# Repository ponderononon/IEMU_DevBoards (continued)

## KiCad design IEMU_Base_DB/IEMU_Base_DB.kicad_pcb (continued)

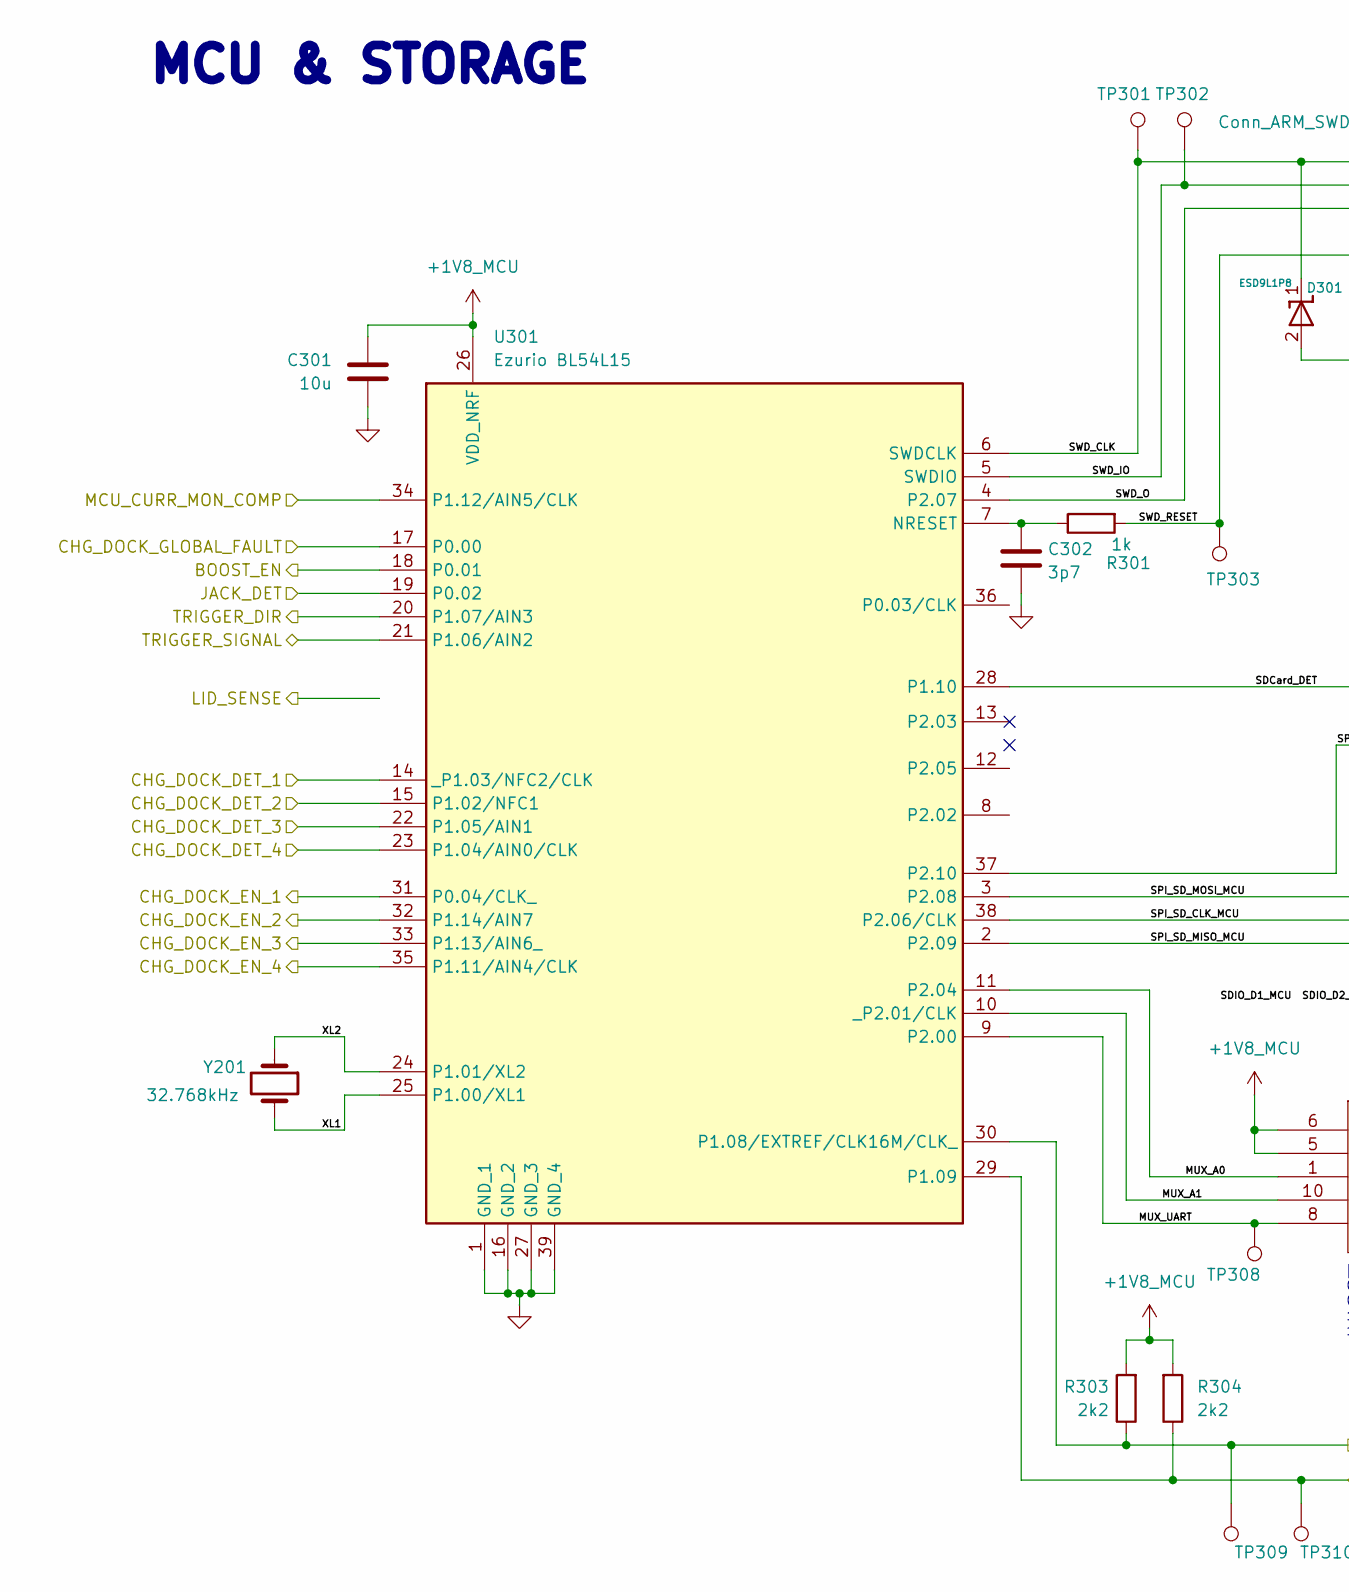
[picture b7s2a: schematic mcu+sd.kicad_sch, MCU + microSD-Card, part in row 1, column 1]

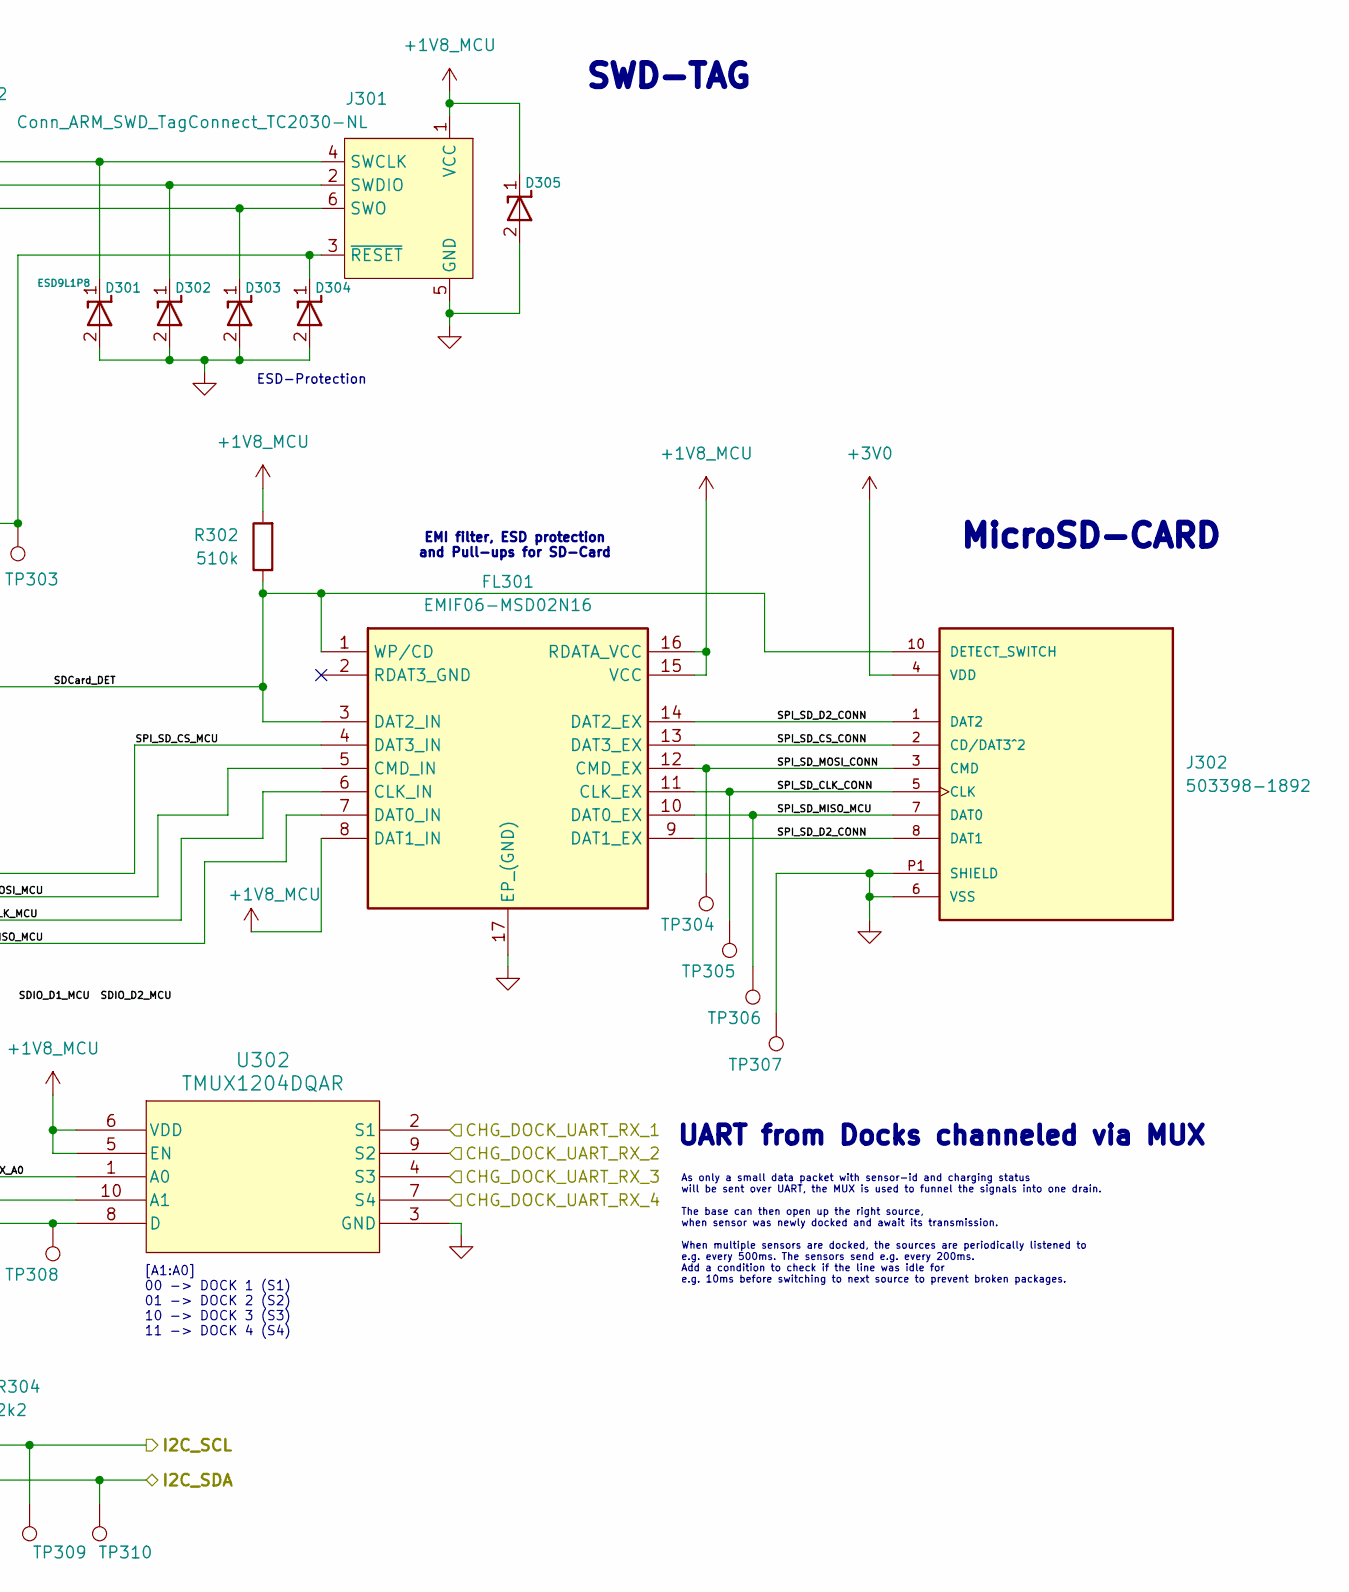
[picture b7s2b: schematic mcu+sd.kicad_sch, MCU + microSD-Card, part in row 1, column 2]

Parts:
C301: 10u; C_0603_1608Metric; Manufacturer_Part_Number CL10A106MA8NRNC; LCSC C96446
C302: 3p7; C_0402_1005Metric; Manufacturer_Part_Number GCM1555C1H3R7CA16D; LCSC C2189484
D301, D302, D303, D304, D305: ESD9L1P8; D_SOD-882; Manufacturer_Part_Number ESD9L1P8; LCSC C6244607
FL301: EMIF06-MSD02N16; EMIF06MSD02N16; Manufacturer_Part_Number EMIF06-MSD02N16; LCSC C5267594
J301: Conn_ARM_SWD_TagConnect_TC2030-NL; Tag-Connect_TC2030-IDC-NL_2x03_P1.27mm_Vertical
J302: 503398-1892; MOLEX_503398-1892; Manufacturer_Part_Number 503398-1892; LCSC C428492
R301: 1k; R_0402_1005Metric; Manufacturer_Part_Number 0402WGF1001TCE; LCSC C11702
R302: 510k; R_0603_1608Metric; Manufacturer_Part_Number 0603WAF5103T5E; LCSC C23192
R303, R304: 2k2; R_0402_1005Metric; Manufacturer_Part_Number 0402WGF2201TCE; LCSC C25879
TP301, TP302, TP303, TP309, TP310: TestPoint_Pad_D1.0mm
TP304, TP305, TP306, TP307, TP308: TestPoint; TestPoint_Pad_D1.0mm
U301: Ezurio BL54L15; BL54L15; Manufacturer_Part_Number 453-00001C
U302: TMUX1204DQAR; IC_TPD4EUSB30DQAR; Manufacturer_Part_Number TMUX1204DQAR; LCSC C1849379
Y201: 32.768kHz; Crystal_SMD_3215-2Pin_3.2x1.5mm; Manufacturer_Part_Number SC-32S32.768kHz20PPM9pF; LCSC C97605

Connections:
+1V8_MCU: C301.1, D305.1 (I/O), FL301.8 (DAT1_IN), FL301.15 (VCC), FL301.16 (RDATA_VCC), J301.1 (VCC), R302.1, R303.1, R304.1, U301.26 (VDD_NRF), U302.5 (EN), U302.6 (VDD); also elsewhere on the board
+3V0: J302.4 (VDD); also elsewhere on the board
/1_Power/BOOST_EN: U301.18 (P0.01); also elsewhere on the board
/1_Power/MCU_CURR_MON_COMP: U301.34 (P1.12/AIN5/CLK); also elsewhere on the board
/1_Power/NPM_SCL: R303.2, TP309.1, U301.30 (P1.08/EXTREF/CLK16M/CLK_); also elsewhere on the board
/1_Power/NPM_SDA: R304.2, TP310.1, U301.29 (P1.09); also elsewhere on the board
/2_Charging_Connections/CHG_DOCK_DET_1: U301.14 (_P1.03/NFC2/CLK); also elsewhere on the board
/2_Charging_Connections/CHG_DOCK_DET_2: U301.15 (P1.02/NFC1); also elsewhere on the board
/2_Charging_Connections/CHG_DOCK_DET_3: U301.22 (P1.05/AIN1); also elsewhere on the board
/2_Charging_Connections/CHG_DOCK_DET_4: U301.23 (P1.04/AIN0/CLK); also elsewhere on the board
/2_Charging_Connections/CHG_DOCK_EN_1: U301.31 (P0.04/CLK_); also elsewhere on the board
/2_Charging_Connections/CHG_DOCK_EN_2: U301.32 (P1.14/AIN7); also elsewhere on the board
/2_Charging_Connections/CHG_DOCK_EN_3: U301.33 (P1.13/AIN6_); also elsewhere on the board
/2_Charging_Connections/CHG_DOCK_EN_4: U301.35 (P1.11/AIN4/CLK); also elsewhere on the board
/2_Charging_Connections/CHG_DOCK_GLOBAL_FAULT: U301.17 (P0.00); also elsewhere on the board
/2_Charging_Connections/CHG_DOCK_UART_RX_1: U302.2 (S1); also elsewhere on the board
/2_Charging_Connections/CHG_DOCK_UART_RX_2: U302.9 (S2); also elsewhere on the board
/2_Charging_Connections/CHG_DOCK_UART_RX_3: U302.4 (S3); also elsewhere on the board
/2_Charging_Connections/CHG_DOCK_UART_RX_4: U302.7 (S4); also elsewhere on the board
/3_nRF Module & SDCard/JACK_DET: U301.19 (P0.02); also elsewhere on the board
/3_nRF Module & SDCard/MUX_A0: U301.11 (P2.04), U302.1 (A0)
/3_nRF Module & SDCard/MUX_A1: U301.10 (_P2.01/CLK), U302.10 (A1)
/3_nRF Module & SDCard/MUX_UART: TP308.1, U301.9 (P2.00), U302.8 (D)
/3_nRF Module & SDCard/SDCard_DET: FL301.1 (WP/CD), FL301.3 (DAT2_IN), J302.10 (DETECT_SWITCH), R302.2, U301.28 (P1.10)
/3_nRF Module & SDCard/SPI_SD_CLK_CONN: FL301.11 (CLK_EX), J302.5 (CLK), TP305.1
/3_nRF Module & SDCard/SPI_SD_CLK_MCU: FL301.6 (CLK_IN), U301.38 (P2.06/CLK)
/3_nRF Module & SDCard/SPI_SD_CS_CONN: FL301.13 (DAT3_EX), J302.2 (CD/DAT3^2)
/3_nRF Module & SDCard/SPI_SD_CS_MCU: FL301.4 (DAT3_IN), U301.37 (P2.10)
/3_nRF Module & SDCard/SPI_SD_D2_CONN: FL301.9 (DAT1_EX), FL301.14 (DAT2_EX), J302.1 (DAT2), J302.8 (DAT1)
/3_nRF Module & SDCard/SPI_SD_MISO_MCU: FL301.7 (DAT0_IN), FL301.10 (DAT0_EX), J302.7 (DAT0), TP306.1, U301.2 (P2.09)
/3_nRF Module & SDCard/SPI_SD_MOSI_CONN: FL301.12 (CMD_EX), J302.3 (CMD), TP304.1
/3_nRF Module & SDCard/SPI_SD_MOSI_MCU: FL301.5 (CMD_IN), U301.3 (P2.08)
/3_nRF Module & SDCard/SWD_CLK: D301.1 (I/O), J301.4 (SWCLK), TP301.1, U301.6 (SWDCLK)
/3_nRF Module & SDCard/SWD_IO: D302.1 (I/O), J301.2 (SWDIO), TP302.1, U301.5 (SWDIO)
/3_nRF Module & SDCard/SWD_O: D303.1 (I/O), J301.6 (SWO), U301.4 (P2.07)
/3_nRF Module & SDCard/SWD_RESET: D304.1 (I/O), J301.3 (~RESET), R301.1, TP303.1
/3_nRF Module & SDCard/TRIGGER_DIR: U301.20 (P1.07/AIN3); also elsewhere on the board
/3_nRF Module & SDCard/TRIGGER_SIGNAL: U301.21 (P1.06/AIN2); also elsewhere on the board
/3_nRF Module & SDCard/XL1: U301.25 (P1.00/XL1), Y201.2
/3_nRF Module & SDCard/XL2: U301.24 (P1.01/XL2), Y201.1
GND: C301.2, C302.2, D301.2 (GND), D302.2 (GND), D303.2 (GND), D304.2 (GND), D305.2 (GND), FL301.17 (EP_(GND)), J301.5 (GND), J302.6 (VSS), J302.9 (VSS), J302.P1 (SHIELD), J302.P2 (SHIELD), J302.P3 (SHIELD), J302.P4 (SHIELD), TP307.1, U301.1 (GND_1), U301.16 (GND_2), U301.27 (GND_3), U301.39 (GND_4), U302.3 (GND); also elsewhere on the board
unnamed: C302.1, R301.2, U301.7 (NRESET)

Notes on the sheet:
As only a small data packet with sensor-id and charging status will be sent over UART, the MUX is used to funnel the signals into one drain. The base can then open up the right source, when sensor was newly docked and await its transmission. When multiple sensors are docked, the sources are periodi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
SWD-TAG
UART from Docks channeled via MUX
MCU & STORAGE
MicroSD-CARD
EMI filter, ESD protection and Pull-ups for SD-Card
[A1:A0] 00 -> DOCK 1 (S1) 01 -> DOCK 2 (S2) 10 -> DOCK 3 (S3) 11 -> DOCK 4 (S4)
ESD-Protection

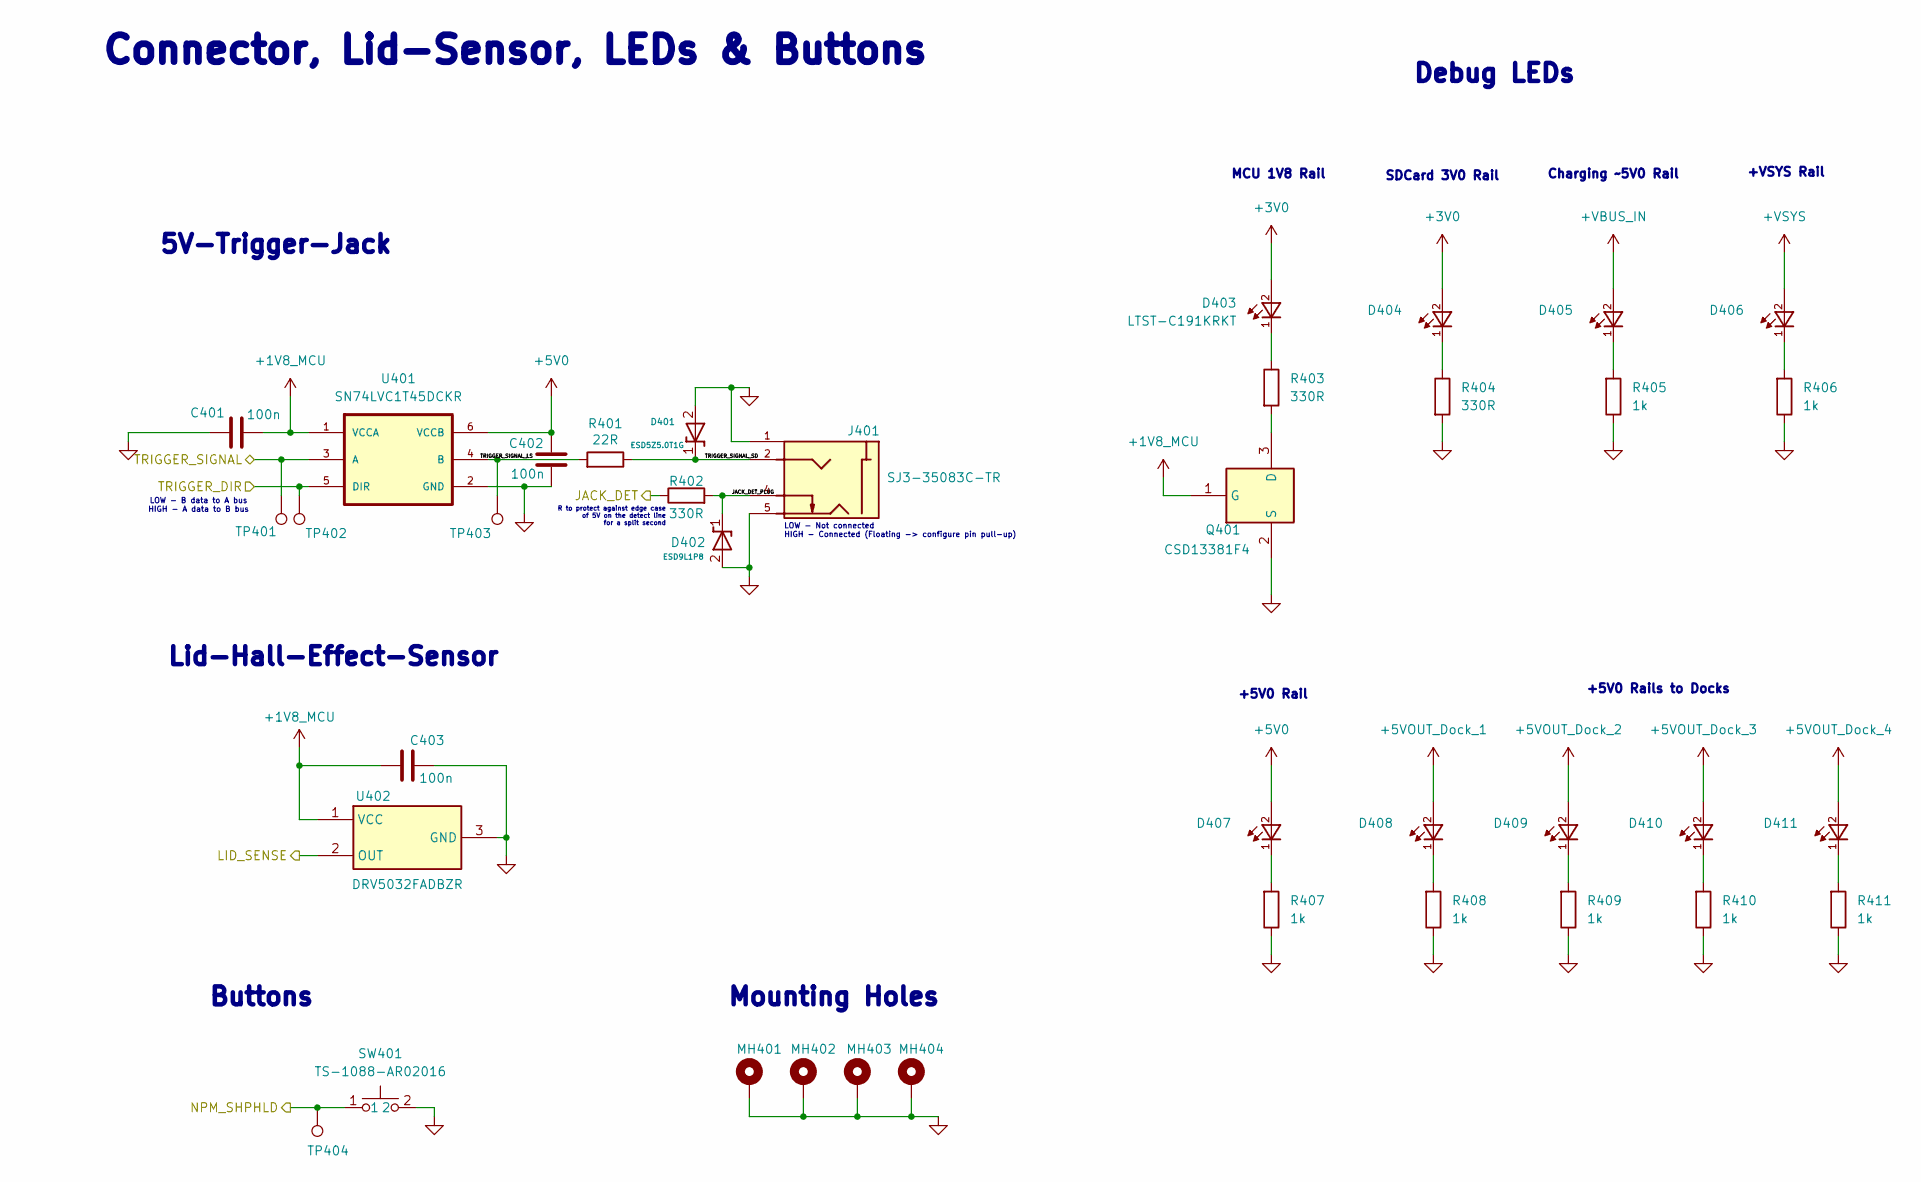
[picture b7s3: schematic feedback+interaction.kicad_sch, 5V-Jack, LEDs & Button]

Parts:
C401, C402: 100n; C_0402_1005Metric; Manufacturer_Part_Number CL05B104KB54PNC; LCSC C307331
C403: 100n; C_0402_1005Metric; Manufacturer_Part_Number CL05B104KO5NNNC; LCSC C1525
D401: ESD5Z5.0T1G; D_SOD-523_1; Manufacturer_Part_Number ESD5Z5.0T1G; LCSC C82044
D402: ESD9L1P8; D_SOD-882; Manufacturer_Part_Number ESD9L1P8; LCSC C6244607
D403, D404, D405, D406, D407, D408, D409, D410, D411: LTST-C191KRKT; Manufacturer_Part_Number LTST-C191KRKT; LCSC C125099
J401: SJ3-35083C-TR; SAMESKY_SJ3-35083C-TR; Manufacturer_Part_Number SJ3-35083C-TR
MH401, MH402, MH403, MH404: MountingHole_Pad; MountingHole_2.2mm_M2_Pad_Via
Q401: CSD13381F4; DFN100X60X35-3N; Manufacturer_Part_Number CSD13381F4; LCSC C179868
R401: 22R; R_0603_1608Metric; Manufacturer_Part_Number 0603WAF220JT5E; LCSC C23345
R402, R403, R404: 330R; R_0402_1005Metric; Manufacturer_Part_Number 0402WGF3300TCE; LCSC C25104
R405, R406, R407, R408, R409, R410, R411: 1k; R_0402_1005Metric; Manufacturer_Part_Number 0402WGF1001TCE; LCSC C11702
SW401: TS-1088-AR02016; SW_TS-1088-AR02016; Manufacturer_Part_Number TS-1088-AR02016; LCSC C720477
TP401, TP402, TP403, TP404: TestPoint_Pad_D1.0mm
U401: SN74LVC1T45DCKR; SOT-363_SC-70-6; Manufacturer_Part_Number SN74LVC1T45DCKR; LCSC C9382
U402: DRV5032FADBZR; SOT-23; Manufacturer_Part_Number DRV5032FADBZR; LCSC C140921

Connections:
+1V8_MCU: C401.2, C403.1, Q401.1 (G), U401.1 (VCCA), U402.1 (VCC); also elsewhere on the board
+3V0: D403.2, D404.2; also elsewhere on the board
+5V0: C402.1, D407.2, U401.6 (VCCB); also elsewhere on the board
+5VOUT_Dock_1: D408.2; also elsewhere on the board
+5VOUT_Dock_2: D409.2; also elsewhere on the board
+5VOUT_Dock_3: D410.2; also elsewhere on the board
+5VOUT_Dock_4: D411.2; also elsewhere on the board
+VBUS_IN: D405.2; also elsewhere on the board
+VSYS: D406.2; also elsewhere on the board
/1_Power/NPM_SHPHLD: SW401.1, TP404.1; also elsewhere on the board
/3_nRF Module & SDCard/JACK_DET: R402.1; also elsewhere on the board
/3_nRF Module & SDCard/LID_SENSE: U402.2 (OUT)
/3_nRF Module & SDCard/TRIGGER_DIR: TP402.1, U401.5 (DIR); also elsewhere on the board
/3_nRF Module & SDCard/TRIGGER_SIGNAL: TP401.1, U401.3 (A); also elsewhere on the board
/4_5V_Jack, Lid-Sensor, LEDs & Button/JACK_DET_PLUG: D402.1 (I/O), J401.4, R402.2
/4_5V_Jack, Lid-Sensor, LEDs & Button/TRIGGER_SIGNAL_LS: R401.1, TP403.1, U401.4 (B)
/4_5V_Jack, Lid-Sensor, LEDs & Button/TRIGGER_SIGNAL_SD: D401.1 (I/O), J401.2, R401.2
GND: C401.1, C402.2, C403.2, D401.2 (GND), D402.2 (GND), J401.1, J401.5, MH401.1, MH402.1, MH403.1, MH404.1, Q401.2 (S), R404.2, R405.2, R406.2, R407.2, R408.2, R409.2, R410.2, R411.2, SW401.2, U401.2 (GND), U402.3 (GND); also elsewhere on the board
unnamed: D403.1, R403.1
unnamed: D404.1, R404.1
unnamed: D405.1, R405.1
unnamed: D406.1, R406.1
unnamed: D407.1, R407.1
unnamed: D408.1, R408.1
unnamed: D409.1, R409.1
unnamed: D410.1, R410.1
unnamed: D411.1, R411.1
unnamed: Q401.3 (D), R403.2

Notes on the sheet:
SDCard 3V0 Rail
Mounting Holes
Buttons
+5V0 Rail
Connector, Lid-Sensor, LEDs & Buttons
5V-Trigger-Jack
R to protect against edge case of 5V on the detect line for a split second
Lid-Hall-Effect-Sensor
+VSYS Rail
MCU 1V8 Rail
LOW - Not connected HIGH - Connected (Floating -> configure pin pull-up)
Charging ~5V0 Rail
+5V0 Rails to Docks
Debug LEDs
LOW - B data to A bus HIGH - A data to B bus

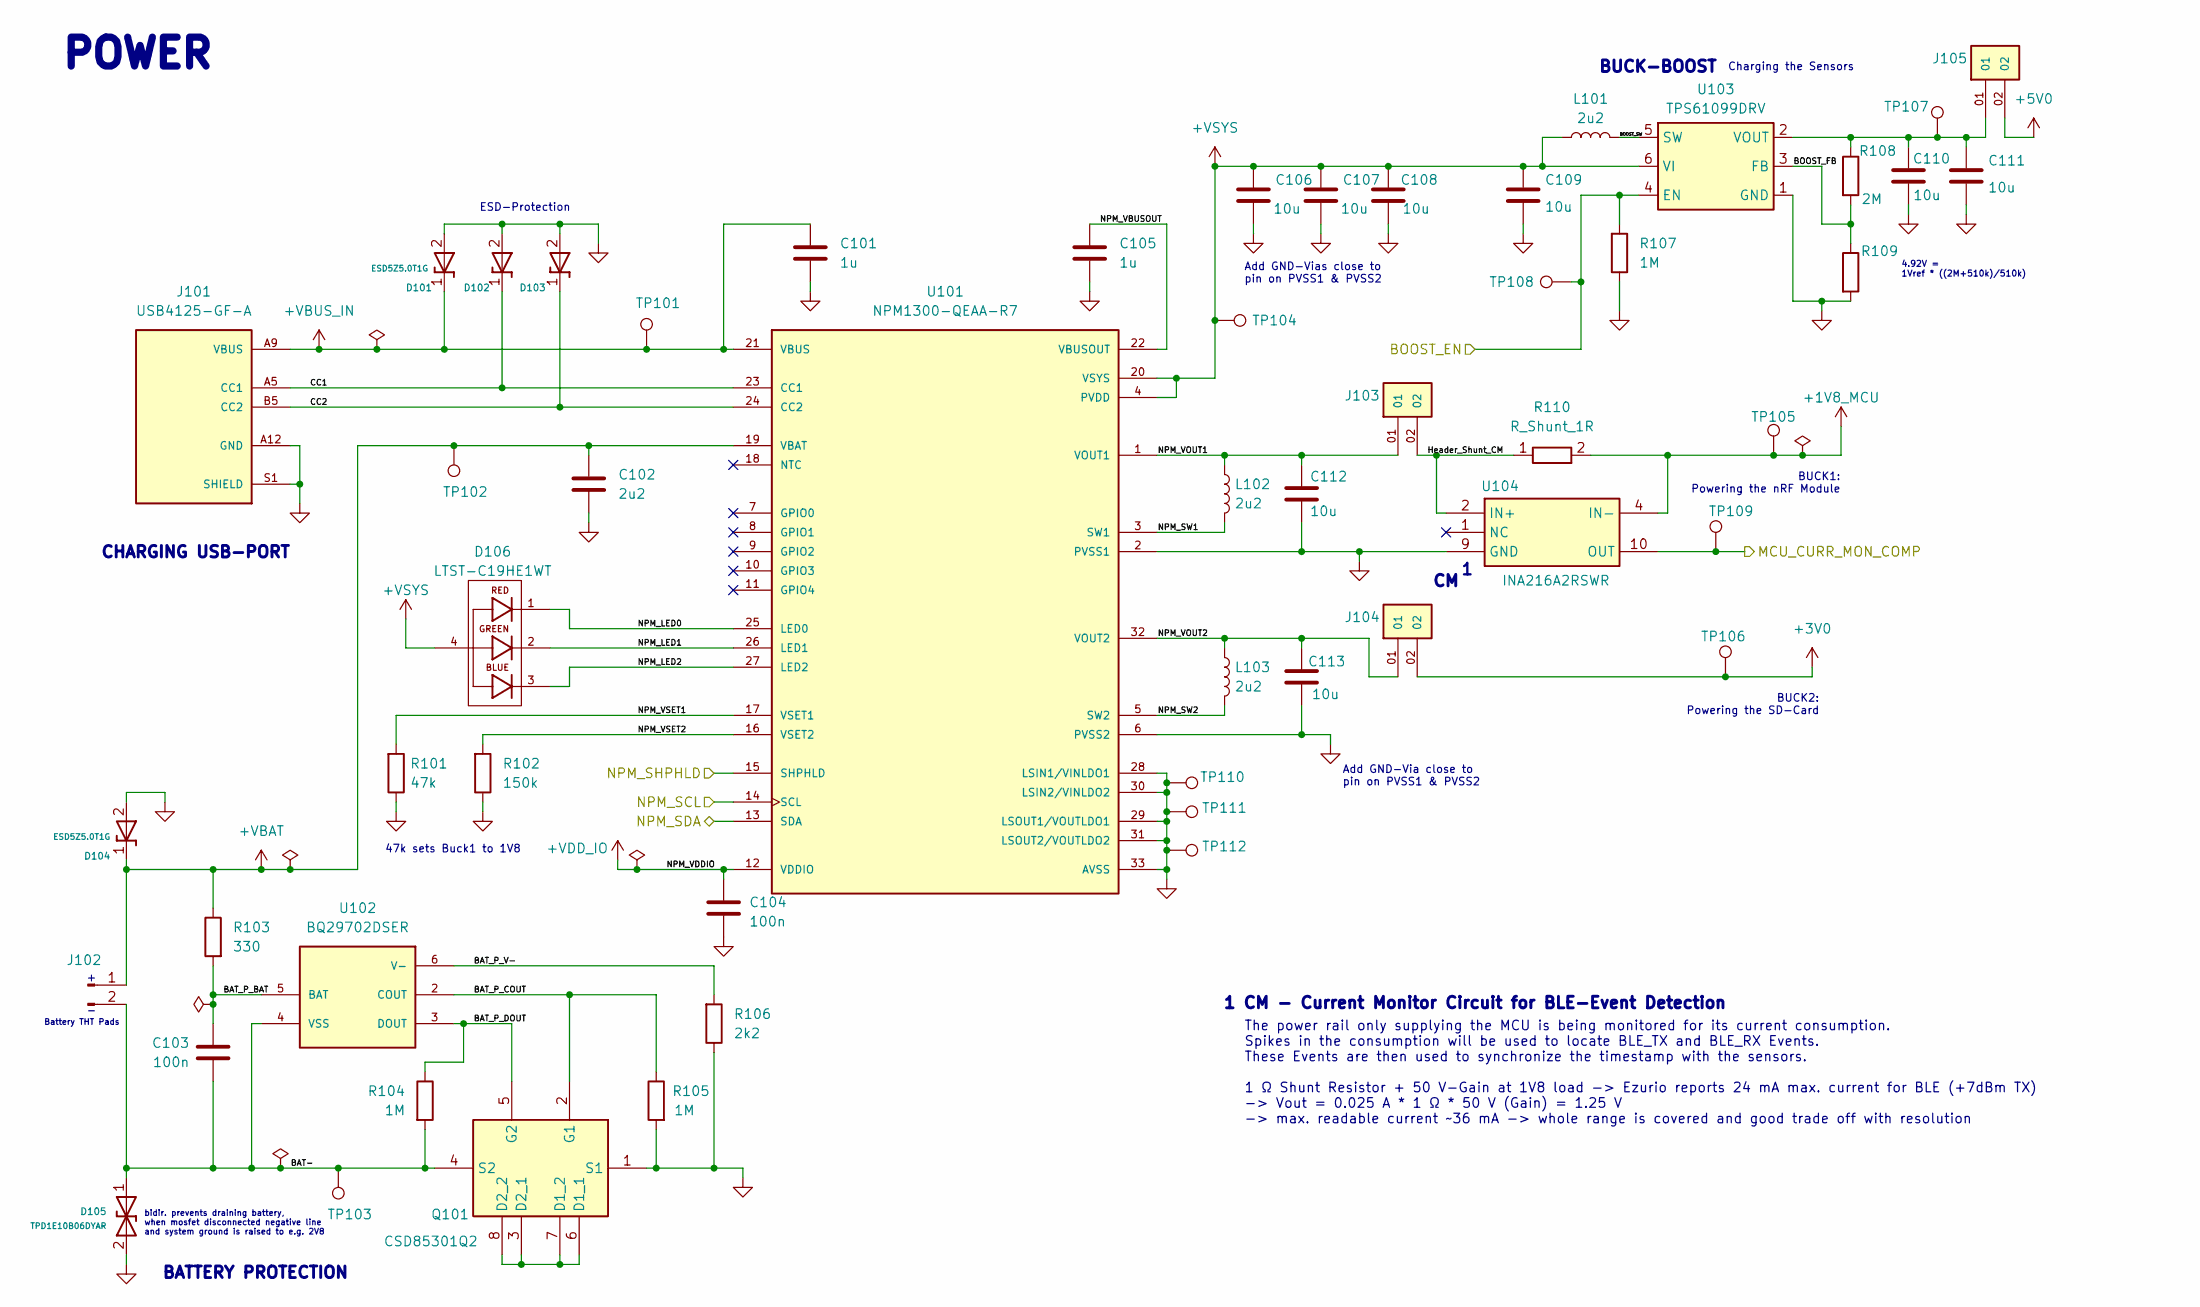
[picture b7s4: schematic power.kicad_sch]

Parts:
C101, C105: 1u; C_0402_1005Metric; Manufacturer_Part_Number CL05A105KA5NQNC; LCSC C52923
C102: 2u2; C_0402_1005Metric; Manufacturer_Part_Number CL05A225MQ5NSNC; LCSC C12530
C103, C104: 100n; C_0402_1005Metric; Manufacturer_Part_Number CL05B104KO5NNNC; LCSC C1525
C106, C107, C108, C109, C110, C111, C112, C113: 10u; C_0603_1608Metric; Manufacturer_Part_Number CL10A106MA8NRNC; LCSC C96446
D101, D102, D103, D104: ESD5Z5.0T1G; D_SOD-523_1; Manufacturer_Part_Number ESD5Z5.0T1G; LCSC C82044
D105: TPD1E10B06DYAR; D_SOD-523; Manufacturer_Part_Number TPD1E10B06DYAR; LCSC C3712135
D106: LTST-C19HE1WT; LED_LTST-C19HE1WT; Manufacturer_Part_Number LTST-C19HE1WT; LCSC C458749
J101: USB4125-GF-A; GCT_USB4125-GF-A_REVA2; Manufacturer_Part_Number USB4125-GF-A; LCSC C3151650
J102: Conn_01x02_Pin; SolderWire-0.5sqmm_1x02_P4.6mm_D0.9mm_OD2.1mm
J103, J104, J105: SAMTEC_MTSW-101-X-X-D-X; Manufacturer_Part_Number MTSW-101-07-T-D-240
L101, L102, L103: 2u2; L_0603_1608Metric; Manufacturer_Part_Number LSCNB1608HKT2R2MD; LCSC C6079477
Q101: CSD85301Q2; Manufacturer_Part_Number CSD85301Q2; LCSC C544396
R101: 47k; R_0402_1005Metric; Manufacturer_Part_Number 0402WGF4702TCE; LCSC C25792
R102: 150k; R_0402_1005Metric; Manufacturer_Part_Number 0402WGF1503TCE; LCSC C25755
R103: 330; R_0402_1005Metric; Manufacturer_Part_Number 0402WGF3300TCE; LCSC C25104
R104, R105, R107: 1M; R_0402_1005Metric; Manufacturer_Part_Number 0402WGF1004TCE; LCSC C26083
R106: 2k2; R_0402_1005Metric; Manufacturer_Part_Number 0402WGF2201TCE; LCSC C25879
R108: 2M; R_0603_1608Metric; Manufacturer_Part_Number 0603WAF2004T5E; LCSC C22976
R109: 510k; R_0603_1608Metric; Manufacturer_Part_Number 0603WAF5103T5E; LCSC C23192
R110: R_Shunt_1R; R_0402_1005Metric; Manufacturer_Part_Number RLP73K1E1R0FTDF; LCSC C2074826
TP101, TP102, TP103, TP104, TP105, TP106, TP107, TP108, TP109, TP110, TP111, TP112: TestPoint_Pad_D1.0mm
U101: NPM1300-QEAA-R7; QFN50P500X500X90-33N; Manufacturer_Part_Number NPM1300-QEAA-R7; LCSC C7501206
U102: BQ29702DSER; WSON-6_1.5x1.5mm_P0.5mm; Manufacturer_Part_Number BQ29702DSER; LCSC C2872632
U103: TPS61099DRV; WSON-6-1EP_2x2mm_P0.65mm_EP1x1.6mm; Manufacturer_Part_Number TPS61099DRVR; LCSC C2842395
U104: INA216A2RSWR; Texas_RSW0010A_UQFN-10_1.4x1.8mm_P0.4mm; Manufacturer_Part_Number INA216A2RSWR; LCSC C2653823

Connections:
+1V8_MCU: R110.2, TP105.1, U104.4 (IN-), U104.5 (IN-); also elsewhere on the board
+3V0: J104.02, TP106.1; also elsewhere on the board
+5V0: J105.02; also elsewhere on the board
+VBAT: C102.1, D104.1 (I/O), J102.1, R103.1, TP102.1, U101.19 (VBAT)
+VBUS_IN: C101.1, D101.1 (I/O), J101.A9 (VBUS), J101.B9 (VBUS), TP101.1, U101.21 (VBUS); also elsewhere on the board
+VDD_IO: C104.1, U101.12 (VDDIO)
+VSYS: C106.1, C107.1, C108.1, C109.1, D106.4, L101.1, TP104.1, U101.4 (PVDD), U101.20 (VSYS), U103.6 (VI); also elsewhere on the board
/1_Power/BAT-: C103.2, D105.1 (I/O), J102.2, Q101.4 (S2), R104.1, TP103.1, U102.4 (VSS)
/1_Power/BAT_P_BAT: C103.1, R103.2, U102.5 (BAT)
/1_Power/BAT_P_COUT: Q101.2 (G1), R105.2, U102.2 (COUT)
/1_Power/BAT_P_DOUT: Q101.5 (G2), R104.2, U102.3 (DOUT)
/1_Power/BAT_P_V-: R106.1, U102.6 (V-)
/1_Power/BOOST_EN: R107.1, TP108.1, U103.4 (EN); also elsewhere on the board
/1_Power/BOOST_FB: R108.1, R109.2, U103.3 (FB)
/1_Power/BOOST_SW: L101.2, U103.5 (SW)
/1_Power/CC1: D102.1 (I/O), J101.A5 (CC1), U101.23 (CC1)
/1_Power/CC2: D103.1 (I/O), J101.B5 (CC2), U101.24 (CC2)
/1_Power/Header_Shunt_CM: J103.02, R110.1, U104.2 (IN+), U104.3 (IN+)
/1_Power/MCU_CURR_MON_COMP: TP109.1, U104.10 (OUT); also elsewhere on the board
/1_Power/NPM_LED0: D106.1, U101.25 (LED0)
/1_Power/NPM_LED1: D106.2, U101.26 (LED1)
/1_Power/NPM_LED2: D106.3, U101.27 (LED2)
/1_Power/NPM_SCL: U101.14 (SCL); also elsewhere on the board
/1_Power/NPM_SDA: U101.13 (SDA); also elsewhere on the board
/1_Power/NPM_SHPHLD: U101.15 (SHPHLD); also elsewhere on the board
/1_Power/NPM_SW1: L102.2, U101.3 (SW1)
/1_Power/NPM_SW2: L103.2, U101.5 (SW2)
/1_Power/NPM_VBUSOUT: C105.1, U101.22 (VBUSOUT)
/1_Power/NPM_VOUT1: C112.1, J103.01, L102.1, U101.1 (VOUT1)
/1_Power/NPM_VOUT2: C113.1, J104.01, L103.1, U101.32 (VOUT2)
/1_Power/NPM_VSET1: R101.1, U101.17 (VSET1)
/1_Power/NPM_VSET2: R102.1, U101.16 (VSET2)
GND: C101.2, C102.2, C104.2, C105.2, C106.2, C107.2, C108.2, C109.2, C110.2, C111.2, C112.2, C113.2, D101.2 (GND), D102.2 (GND), D103.2 (GND), D104.2 (GND), D105.2 (GND), J101.A12 (GND), J101.B12 (GND), J101.S1 (SHIELD), J101.S2 (SHIELD), J101.S3 (SHIELD), J101.S4 (SHIELD), Q101.1 (S1), R101.2, R102.2, R105.1, R106.2, R107.2, R109.1, TP110.1, TP111.1, TP112.1, U101.2 (PVSS1), U101.6 (PVSS2), U101.28 (LSIN1/VINLDO1), U101.29 (LSOUT1/VOUTLDO1), U101.30 (LSIN2/VINLDO2), U101.31 (LSOUT2/VOUTLDO2), U101.33 (AVSS), U103.1 (GND), U103.7 (GND), U104.9 (GND); also elsewhere on the board
unnamed: Q101.3 (D2_1), Q101.6 (D1_1), Q101.7 (D1_2), Q101.8 (D2_2)
unnamed: C110.1, C111.1, J105.01, R108.2, TP107.1, U103.2 (VOUT)

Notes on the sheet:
POWER
bidir. prevents draining battery, when mosfet disconnected negative line and system ground is raised to e.g. 2V8
Charging the Sensors
4.92V = 1Vref * ((2M+510k)/510k)
BUCK1: Powering the nRF Module
47k sets Buck1 to 1V8
CHARGING USB-PORT
ESD-Protection
Battery THT Pads
Add GND-Vias close to pin on PVSS1 & PVSS2
1 CM - Current Monitor Circuit for BLE-Event Detection
BUCK2: Powering the SD-Card
Add GND-Via close to pin on PVSS1 & PVSS2
BATTERY PROTECTION
BUCK-BOOST
The power rail only supplying the MCU is being monitored for its current consumption. Spikes in the consumption will be used to locate BLE_TX and BLE_RX Events. These Events are then used to synchronize the timestamp with the sensors. 1 Ω Shunt Resistor + 50 V-Gain at 1V8 load -> Ezurio reports 24 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
